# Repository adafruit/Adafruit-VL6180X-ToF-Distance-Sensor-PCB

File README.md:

## Adafruit VL6180X ToF Distance Sensor PCB

<a href="http://www.adafruit.com/products/3316"><br/>
Click here to purchase one from the Adafruit shop</a>

PCB files for the Adafruit VL6180X (VL6180) ToF Distance Sensor. Format is EagleCAD schematic and board layout

For more details, check out the product page at
* https://www.adafruit.com/product/3316

### Description

The VL6180X (sometimes called the VL6180) is a Time of Flight distance sensor like no other you've used! The sensor contains a very tiny laser source, and a matching sensor. The VL6180X can detect the "time of flight", or how long the laser light has taken to bounce back to the sensor. Since it uses a very narrow light source, it is good for determining distance of only the surface directly in front of it.

Unlike sonars that bounce ultrasonic waves, the 'cone' of sensing is very narrow. Unlike IR distance sensors that try to measure the amount of light bounced, the VL6180X is much more precise and doesn't have linearity problems or 'double imaging' where you can't tell if an object is very far or very close.

This is the 'little sister' of the Adafruit VL53L0X ToF sensor, and can handle about 5mm to 100mm of range distance. We've seen up to 150-200mm with good ambient conditions. It also includes a lux sensor. If you need a larger range, check out the VL53L0X which can measure 50 - 1200 mm.

The sensor is small and easy to use in any robotics or interactive project. Since it needs 2.8V power and logic we put the little fellow on a breakout board with a regulator and level shifting. You can use it with any 3-5V power or logic microcontroller with no worries. Each order comes with a small piece of header. Solder the header onto your breakout board with your iron and some solder and wire it up for instant distance-sensing-success!

Communicating to the sensor is done over I2C with some simple commands. Most of the work is handled inside the sensor itself, so its very easy to port our Arduino library to another microcontroller.

### License

Adafruit invests time and resources providing this open source design, please support Adafruit and open-source hardware by purchasing products from [Adafruit](https://www.adafruit.com)!

Designed by Limor Fried/Ladyada for Adafruit Industries.

Creative Commons Attribution/Share-Alike, all text above must be included in any redistribution. See license.txt for additional details.

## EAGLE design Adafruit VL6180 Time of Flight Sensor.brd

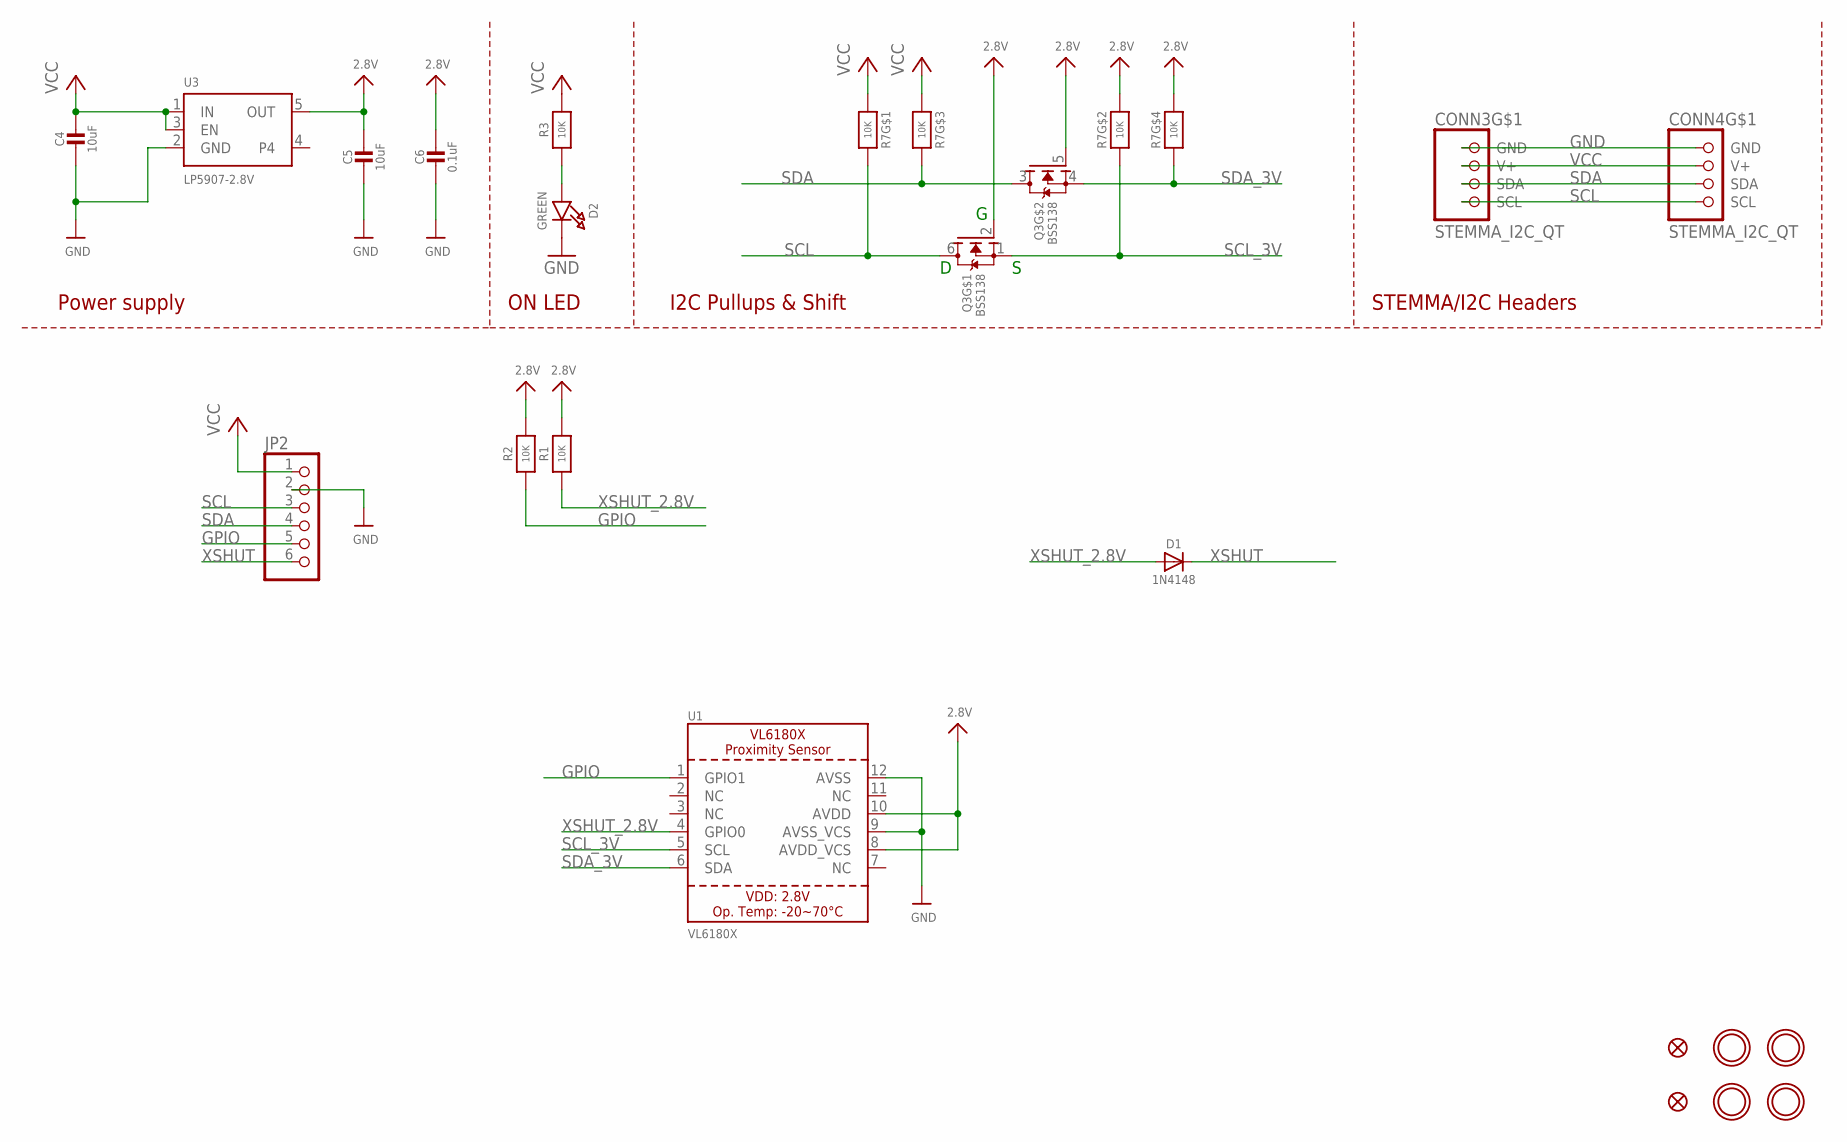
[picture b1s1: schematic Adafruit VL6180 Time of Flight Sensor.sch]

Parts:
C4, C5: 10uF; 0805-NO
C6: 0.1uF; 0603-NO
CONN3, CONN4: STEMMA_I2C_QT; JST_SH4
D1: 1N4148; SOD-323
D2: GREEN; CHIPLED_0603_NOOUTLINE
FID1, FID4: FIDUCIAL_1MM
JP2: HEADER-1X670MIL; 1X06_ROUND_70
Q3: BSS138; SOT363
R1, R2, R3: 10K; 0603-NO
R7: 10K; RESPACK_4X0603
U1: VL6180X; VL6180
U3: LP5907-2.8V; SOT23-5
U$30, U$31, U$33, U$34: MOUNTINGHOLE2.5; MOUNTINGHOLE_2.5_PLATED

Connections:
2.8V: C5.1, C6.1, Q3.2 (G), Q3.5 (G), R1.2, R2.2, R7.2 (1), R7.4 (1), U1.8 (AVDD_VCS), U1.10 (AVDD), U3.5 (OUT)
GND: C4.2, C5.2, C6.2, CONN3.1 (GND), CONN4.1 (GND), D2.C, JP2.2, U1.9 (AVSS_VCS), U1.12 (AVSS), U3.2 (GND)
GPIO: JP2.5, R2.1, U1.1 (GPIO1)
unnamed: D2.A, R3.1
SCL: CONN3.4 (SCL), CONN4.4 (SCL), JP2.3, Q3.6 (D), R7.8 (2)
SCL_3V: Q3.1 (S), R7.7 (2), U1.5 (SCL)
SDA: CONN3.3 (SDA), CONN4.3 (SDA), JP2.4, Q3.3 (D), R7.6 (2)
SDA_3V: Q3.4 (S), R7.5 (2), U1.6 (SDA)
VCC: C4.1, CONN3.2 (V+), CONN4.2 (V+), JP2.1, R3.2, R7.1, R7.3 (1), U3.1 (IN), U3.3 (EN)
XSHUT: D1.C, JP2.6
XSHUT_2.8V: D1.A, R1.1, U1.4 (GPIO0)

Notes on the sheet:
I2C Pullups & Shift
STEMMA/I2C Headers
ON LED
Power supply

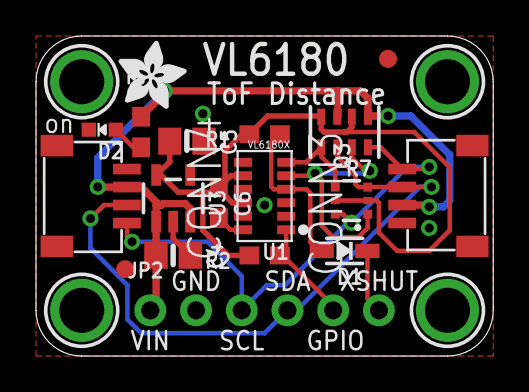
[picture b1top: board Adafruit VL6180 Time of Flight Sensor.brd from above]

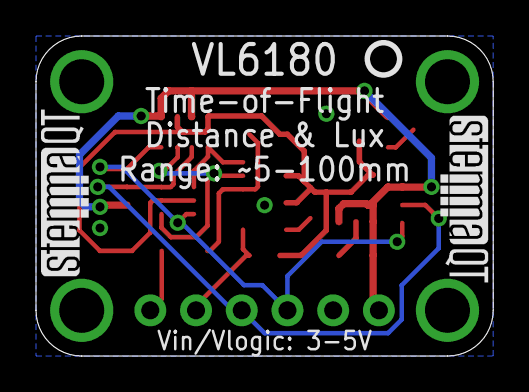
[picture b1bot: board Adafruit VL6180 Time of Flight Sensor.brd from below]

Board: 2 copper layers, 25.4 x 17.8 mm, 25 parts (3 on the bottom side), 11 nets.

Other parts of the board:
U$36: ADAFRUIT_3.5MM
U$37: PCBFEAT-REV-040
U$38, U$39: STEMMAQT

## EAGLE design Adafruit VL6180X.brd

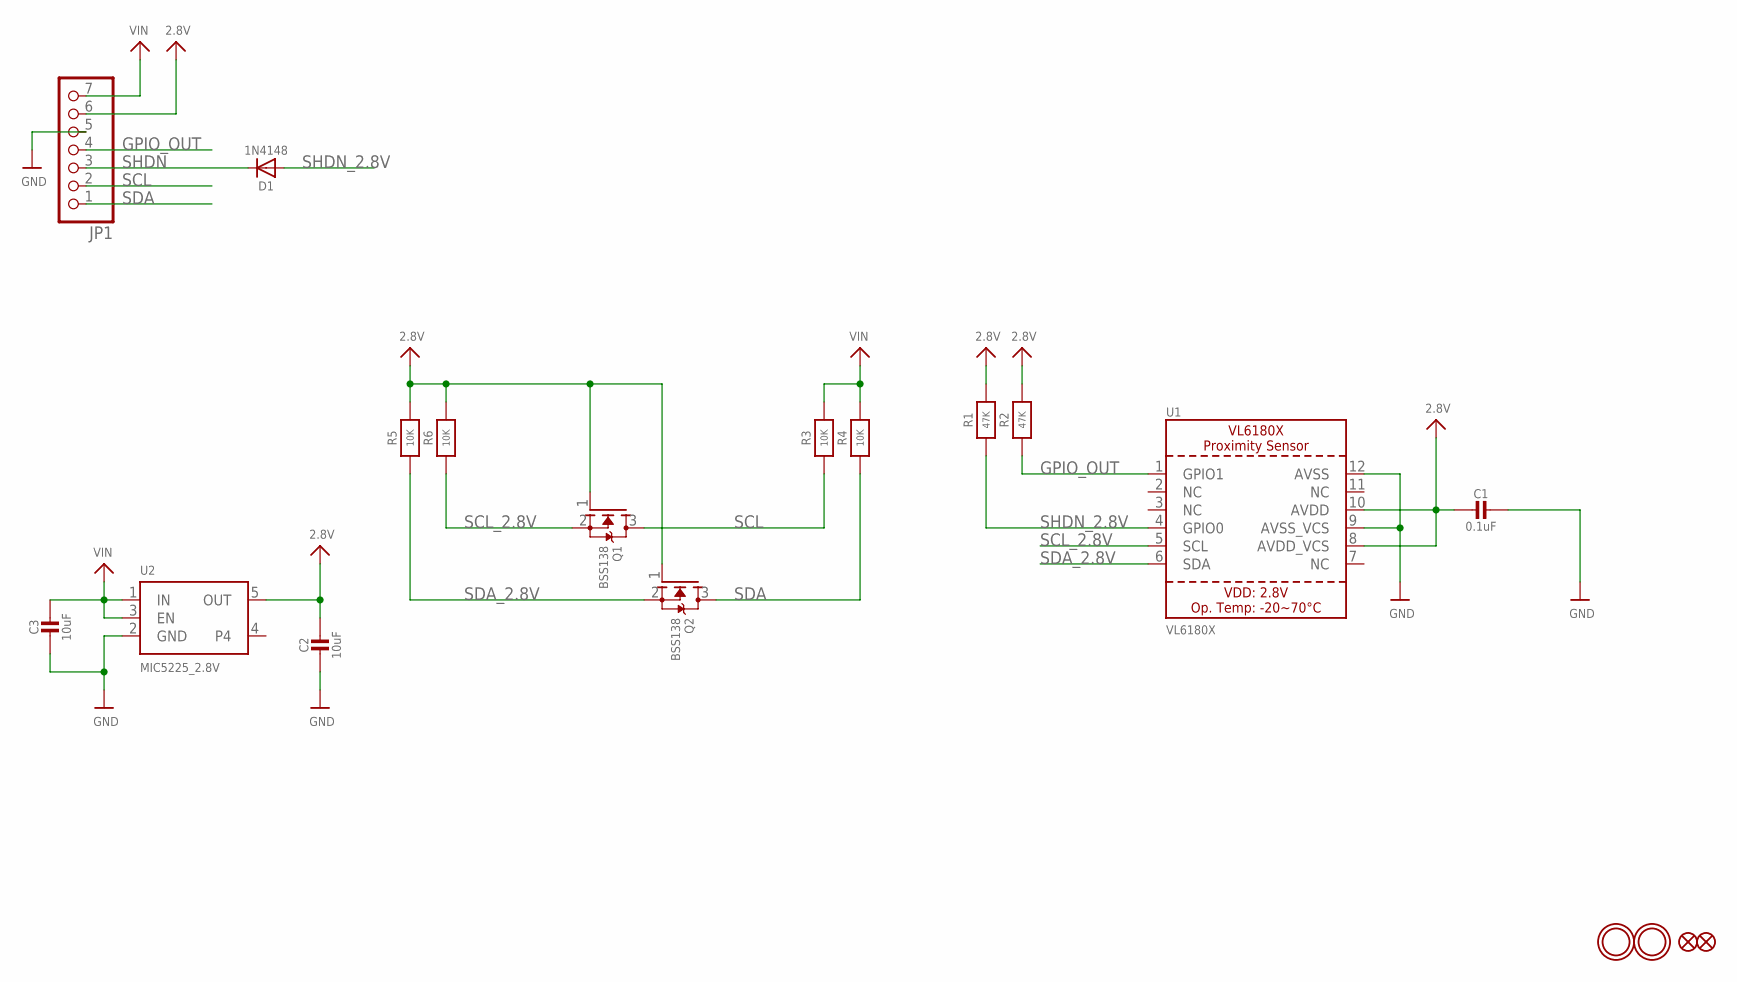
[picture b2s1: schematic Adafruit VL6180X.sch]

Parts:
C1: 0.1uF; 0805-NO
C2, C3: 10uF; 0805-NO
D1: 1N4148; SOD-323
FID1, FID2: FIDUCIAL""; FIDUCIAL_1MM
JP1: HEADER-1X770MIL; 1X07_ROUND_70
Q1, Q2: BSS138; SOT23-WIDE
R1, R2: 47K; 0805-NO
R3, R4, R5, R6: 10K; 0805-NO
U1: VL6180X; VL6180
U2: MIC5225_2.8V; SOT23-5
U$11, U$12: MOUNTINGHOLE2.5; MOUNTINGHOLE_2.5_PLATED

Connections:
2.8V: C1.2, C2.1, JP1.6, Q1.1 (G), Q2.1 (G), R1.2, R2.2, R5.2, R6.2, U1.8 (AVDD_VCS), U1.10 (AVDD), U2.5 (OUT)
GND: C1.1, C2.2, C3.2, JP1.5, U1.9 (AVSS_VCS), U1.12 (AVSS), U2.2 (GND)
GPIO_OUT: JP1.4, R2.1, U1.1 (GPIO1)
SCL: JP1.2, Q1.3 (D), R3.1
SCL_2.8V: Q1.2 (S), R6.1, U1.5 (SCL)
SDA: JP1.1, Q2.3 (D), R4.1
SDA_2.8V: Q2.2 (S), R5.1, U1.6 (SDA)
SHDN: D1.C, JP1.3
SHDN_2.8V: D1.A, R1.1, U1.4 (GPIO0)
VIN: C3.1, JP1.7, R3.2, R4.2, U2.1 (IN), U2.3 (EN)

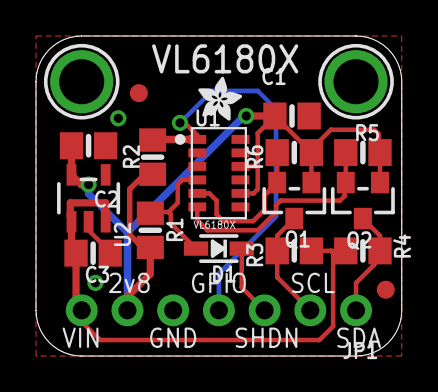
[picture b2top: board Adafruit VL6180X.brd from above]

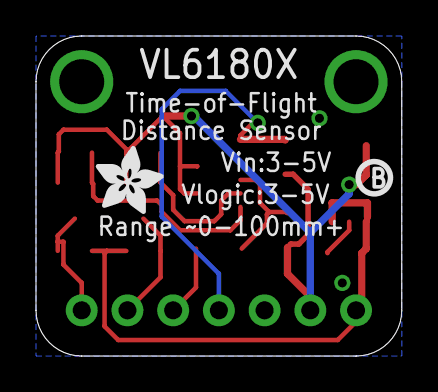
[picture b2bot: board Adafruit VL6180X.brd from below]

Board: 2 copper layers, 20.3 x 17.8 mm, 22 parts (2 on the bottom side), 10 nets.

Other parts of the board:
U$18: ADAFRUIT_2.5MM
U$20: ADAFRUIT_3.5MM
U$21: PCBFEAT-REV-040

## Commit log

2016-11-30 init
2020-03-25 Adding updated board files

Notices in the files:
parts and their libraries:
microbuilder: This work is placed in the public domain, and may be freely used for commercial and non-commercial work with the following conditions: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
